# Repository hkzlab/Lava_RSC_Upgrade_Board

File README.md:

# Lava RSC Lite Upgrade Board

## DISCLAIMER

Any use of this project is **under your own responsibility**.
You will be responsible of checking the correct construction and functionality of your board.
By using this project You will agree that I cannot be held responsible if it will destroy any of your devices, damage your computer, burn down your house or whatever.

I want to stress this out: You're on your own using this. It works for me, I cannot give guarantees to you. Also, **do not go bother the Lava RSC people about it for support!!!**

## Introduction

The [Lava RSC](http://www.lava-fc.top/) is a family of very nice Famiclones that use ICs found in the original Famicom, complemented with an FPGA used to output an analog RGB picture.

From time to time, the people at Lava update the FPGA firmware to fix bugs and add new features.
The high end model, the Lava RSC, includes an SD card slot connected to an MCU, and is capable of updating the FPGA autonomously, while the Lite version requires an FPGA programmer and 
not-so-easy to obtain Anlogic software to complete the update.

This board reproduces the upgrade circuitry found in a Lava RSC, but as an external module. This way it's sufficient to install headers on your Lite motherboard (there are well marked
spots to solder one), if you want, bring out the signals via a flat cable, and connect this adapter when you want to perform the update. The rest works the same as the original Lava RSC
(beside requiring a Lite-specific firmware, of course).

### Ordering the boards

You can order the board for this project at [PCBWay](https://www.pcbway.com/project/shareproject/Lava_RSC_Lite_Famiclone_Upgrade_board_22eeb25e.html) and support me or download 
the gerbers and have them printed wherever you like!!!

## Hardware

The board was designed with [KiCad](https://kicad.org/) EDA.

### Bill of Materials

This board uses mostly SMD components, but the footprint allows for handsoldering.

| Component              | Qty | Type / Value                     | Notes                                                                |
| ---------------------- | --- | -------------------------------- | -------------------------------------------------------------------- |
| R3, R7, R8             |  1  | 10K 0805 resistor                |                                                                      |
| R6                     |  1  | 1K 0805 resistor                 |                                                                      |
| RN1, RN2               |  2  | 4-resistor array 4x0612 (1206)   | Convex package, the resistors are isolated                           |
| C2, C3                 |  2  | 22pF 10V C0G 0805 capacitors     |                                                                      |
| C1, C5, C6-C9          |  6  | 100nF 10V 0805 capacitors        |                                                                      |
| C4, C10                |  2  | 10uF 10V 0805 capacitors         |                                                                      |
| J3                     |  1  | 4pin header, 2.54mm              |                                                                      |
| J4                     |  1  | 6pin header, 2.54mm              | I prefer using angled ones for this                                  |
| XS1                    |  1  | uSD connector                    | You can find compatible ones on [AliExpress](https://aliexpress.com/item/4000033854553.html) |
| Y1                     |  1  | 8Mhz crystal, HC-49SD            |                                                                      |
| U1                     |  1  | STM32F103C8T6, LQFP-48           | A compatible GD32F103C8T6 has been tested and found to be working    |

### Flashing the STM32

In this repository you'll the firmware file `McuFirmware_dump.hex` dumped from my Lava RSC: it will search for a file named `LavaRSC.aje` in the root
of a FAT32 formatted SD card.

You can use an st-link (a clone is fine) to flash this board via the SWD header (J3). Remember to power the board with **3.3V**.

You can use the `st-flash` utility to program the device:
```
st-flash --format ihex write .\McuFirmware_dump.hex
```

or use the STM32 ST-Link Utility software.

### Using the board to update the Lite

1. Format an SD card to FAT32, make sure it is empty and copy the update files in it (with name `LavaRSC.aje`). You'll find a Lite compatible firmware in this repository, equivalent to the Lava RSC firmware 1.7
2. Plug the SD card in the update board
3. Wire the JTAG connector (J4) to the points of the same name on your Lite motherboard. Dupont wires are ok for this
4. Remove any cart inserted in the Lite
5. If connected, remove any wire connected to the SWD header on the upgrade board
6. Power on the Lite. After a few seconds, the LED on the upgrade board should start flashing
7. Wait until the LED stops flashing and remains on
8. Power off the Lite and remove the upgrade board
9. Done

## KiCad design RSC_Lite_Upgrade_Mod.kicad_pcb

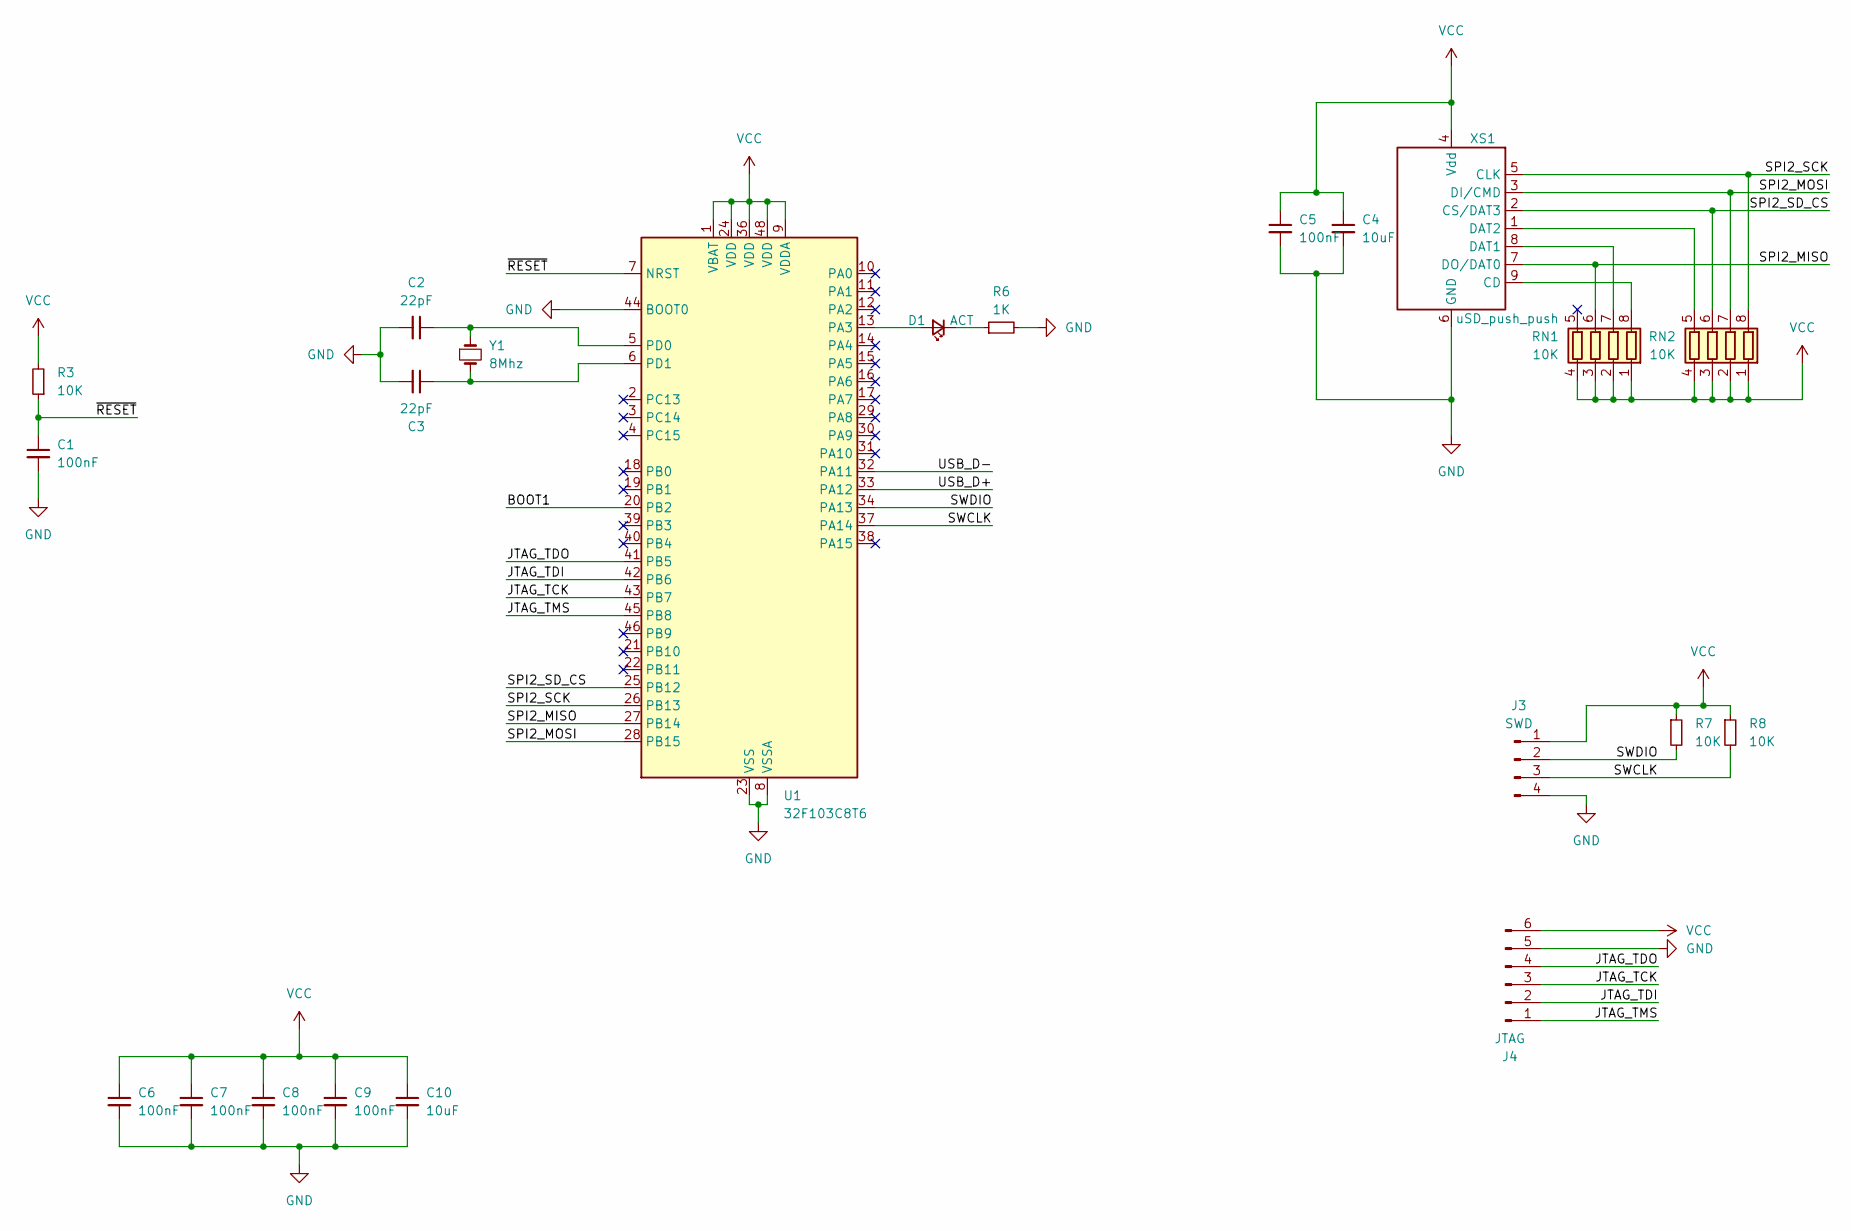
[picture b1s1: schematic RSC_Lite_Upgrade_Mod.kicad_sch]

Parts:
C1, C5, C6, C7, C8, C9: 100nF; C_0805_2012Metric_Pad1.18x1.45mm_HandSolder
C2, C3: 22pF; C_0805_2012Metric_Pad1.18x1.45mm_HandSolder
C4, C10: 10uF; C_0805_2012Metric_Pad1.18x1.45mm_HandSolder
D1: ACT; LED_0805_2012Metric_Pad1.15x1.40mm_HandSolder
J3: SWD; PinHeader_1x04_P2.54mm_Vertical
J4: JTAG; PinHeader_1x06_P2.54mm_Horizontal
R3, R7, R8: 10K; R_0805_2012Metric_Pad1.20x1.40mm_HandSolder
R6: 1K; R_0805_2012Metric_Pad1.20x1.40mm_HandSolder
RN1, RN2: 10K; R_Array_Convex_4x0612
U1: 32F103C8T6; LQFP-48_7x7mm_P0.5mm
XS1: uSD_push_push; Conn_uSDcard
Y1: 8Mhz; Crystal_SMD_HC49-SD

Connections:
/BOOT1: U1.20 (PB2)
/JTAG_TCK: J4.3, U1.43 (PB7)
/JTAG_TDI: J4.2, U1.42 (PB6)
/JTAG_TDO: J4.4, U1.41 (PB5)
/JTAG_TMS: J4.1, U1.45 (PB8)
/SPI2_MISO: RN1.6 (R3.2), U1.27 (PB14), XS1.7 (DO/DAT0)
/SPI2_MOSI: RN2.7 (R2.2), U1.28 (PB15), XS1.3 (DI/CMD)
/SPI2_SCK: RN2.8 (R1.2), U1.26 (PB13), XS1.5 (CLK)
/SPI2_SD_CS: RN2.6 (R3.2), U1.25 (PB12), XS1.2 (CS/DAT3)
/SWCLK: J3.3, R8.2, U1.37 (PA14)
/SWDIO: J3.2, R7.2, U1.34 (PA13)
/USB_D+: U1.33 (PA12)
/USB_D-: U1.32 (PA11)
/~RESET: C1.1, R3.1, U1.7 (NRST)
GND: C1.2, C2.2, C3.2, C4.2, C5.2, C6.2, C7.2, C8.2, C9.2, C10.2, J3.4, J4.5, R6.2, U1.8 (VSSA), U1.23 (VSS), U1.35 (VSS), U1.44 (BOOT0), U1.47 (VSS), XS1.6 (GND)
unnamed: D1.2 (A), U1.13 (PA3)
unnamed: D1.1 (K), R6.1
unnamed: RN1.8 (R1.2), XS1.9 (CD)
unnamed: RN1.7 (R2.2), XS1.8 (DAT1)
unnamed: RN2.5 (R4.2), XS1.1 (DAT2)
unnamed: C2.1, U1.5 (PD0), Y1.1
unnamed: C3.1, U1.6 (PD1), Y1.2
VCC: C4.1, C5.1, C6.1, C7.1, C8.1, C9.1, C10.1, J3.1, J4.6, R3.2, R7.1, R8.1, RN1.1 (R1.1), RN1.2 (R2.1), RN1.3 (R3.1), RN1.4 (R4.1), RN2.1 (R1.1), RN2.2 (R2.1), RN2.3 (R3.1), RN2.4 (R4.1), U1.1 (VBAT), U1.9 (VDDA), U1.24 (VDD), U1.36 (VDD), U1.48 (VDD), XS1.4 (Vdd)

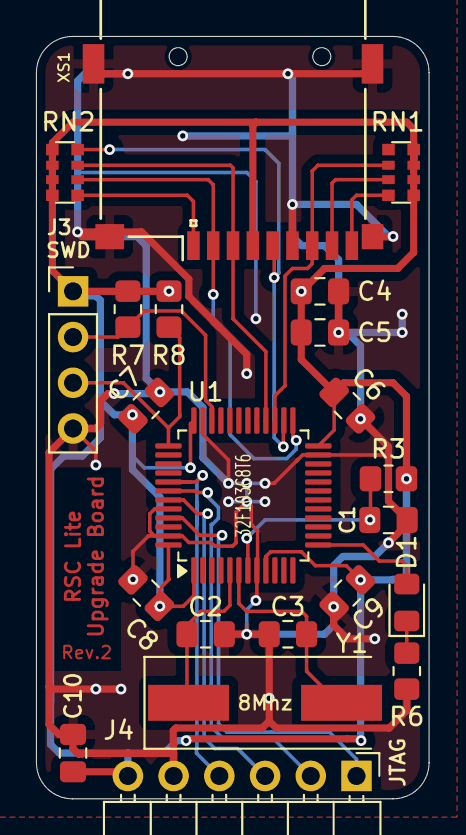
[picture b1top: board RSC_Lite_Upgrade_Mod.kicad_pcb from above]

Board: 2 copper layers, 21.8 x 42.4 mm, 22 parts (0 on the bottom side), 20 nets.

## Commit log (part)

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2025-01-03 :c :x
2025-01-03 Begin drawing the RSC Lite upgrade mod circuit
2025-01-03 Update schematics
2025-01-04 Basic routing for the board
2025-01-04 Update pcb
2025-01-04 Update the PCB
2025-01-04 add another gnd via
2025-01-04 move some silkscreen
2025-01-04 Reorganize some traces
2025-01-04 Add firmware
2025-01-04 Cleanup
2025-01-06 Update PCB layout
2025-01-06 Move some traces around
2025-01-06 Update board and generate gerbers
2025-02-15 Add gerbers and firmware for revision 1
2025-02-15 Add rev.1 schematics
2025-02-15 Begin removing unnecessary components
2025-02-15 Rerouted the board
2025-02-15 Route again
2025-02-15 Update the README
2025-02-15 Add PCBWay project link
2025-02-15 Some more rerouting
2025-02-15 Update some routing and silkscreen
2025-02-16 Reorganize REV.2 board
2025-02-16 Reroute the board, move the jtag connector
2025-02-16 Add new schematics, regenerate gerbers
2025-02-17 Update the BOM
